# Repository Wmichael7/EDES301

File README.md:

# EDES301
Repository for EDES301 course work

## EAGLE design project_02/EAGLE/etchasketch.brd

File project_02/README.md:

# Project 02 - Etch-a-Sketch PCB

## Overview
This project contains the PCB design files for an Etch-a-Sketch device using a PocketBeagle microcontroller. The board features a USB connection, potentiometers for X/Y control, push buttons, and LEDs.

## Project Structure

### `/EAGLE`
Contains the EAGLE PCB design files:
- `etchasketch.sch` - Schematic design
- `etchasketch.brd` - Board layout
- `etchasketch.lbr` - Custom component library

### `/MFG`
Manufacturing files ready for PCB fabrication:

#### `/CAMOutputs/GerberFiles`
- Gerber files for PCB layers (top/bottom copper, soldermask, silkscreen, paste, profile)
- `gerber_job.gbrjob` - Job configuration file

#### `/CAMOutputs/DrillFiles`
- Drill files for PCB holes

#### `/CAMOutputs/Assembly`
- `etchasketch.txt` - Assembly drawing
- `PnP_etchasketch_front.txt` - Front pick-and-place file
- `PnP_etchasketch_back.txt` - Back pick-and-place file

### `/docs`
- `BOM` - Bill of Materials with component specifications

## Bill of Materials

Key components include:
- 1x PocketBeagle microcontroller
- 2x Potentiometers (for X/Y control)
- 2x Push buttons
- 3x LEDs
- 1x USB Type A receptacle connector
- Various resistors
- 4x Mounting holes
- 6x Fiducials

## Getting Started

### Design Files
Open the EAGLE schematic and board files in Autodesk EAGLE to view or modify the design:
1. Open `EAGLE/etchasketch.sch` for schematic
2. Open `EAGLE/etchasketch.brd` for board layout

### Manufacturing
The `/MFG/CAMOutputs` directory contains all files needed to manufacture the PCB:
- Send Gerber files to your PCB manufacturer
- Use the BOM to source components
- Use pick-and-place files for assembly

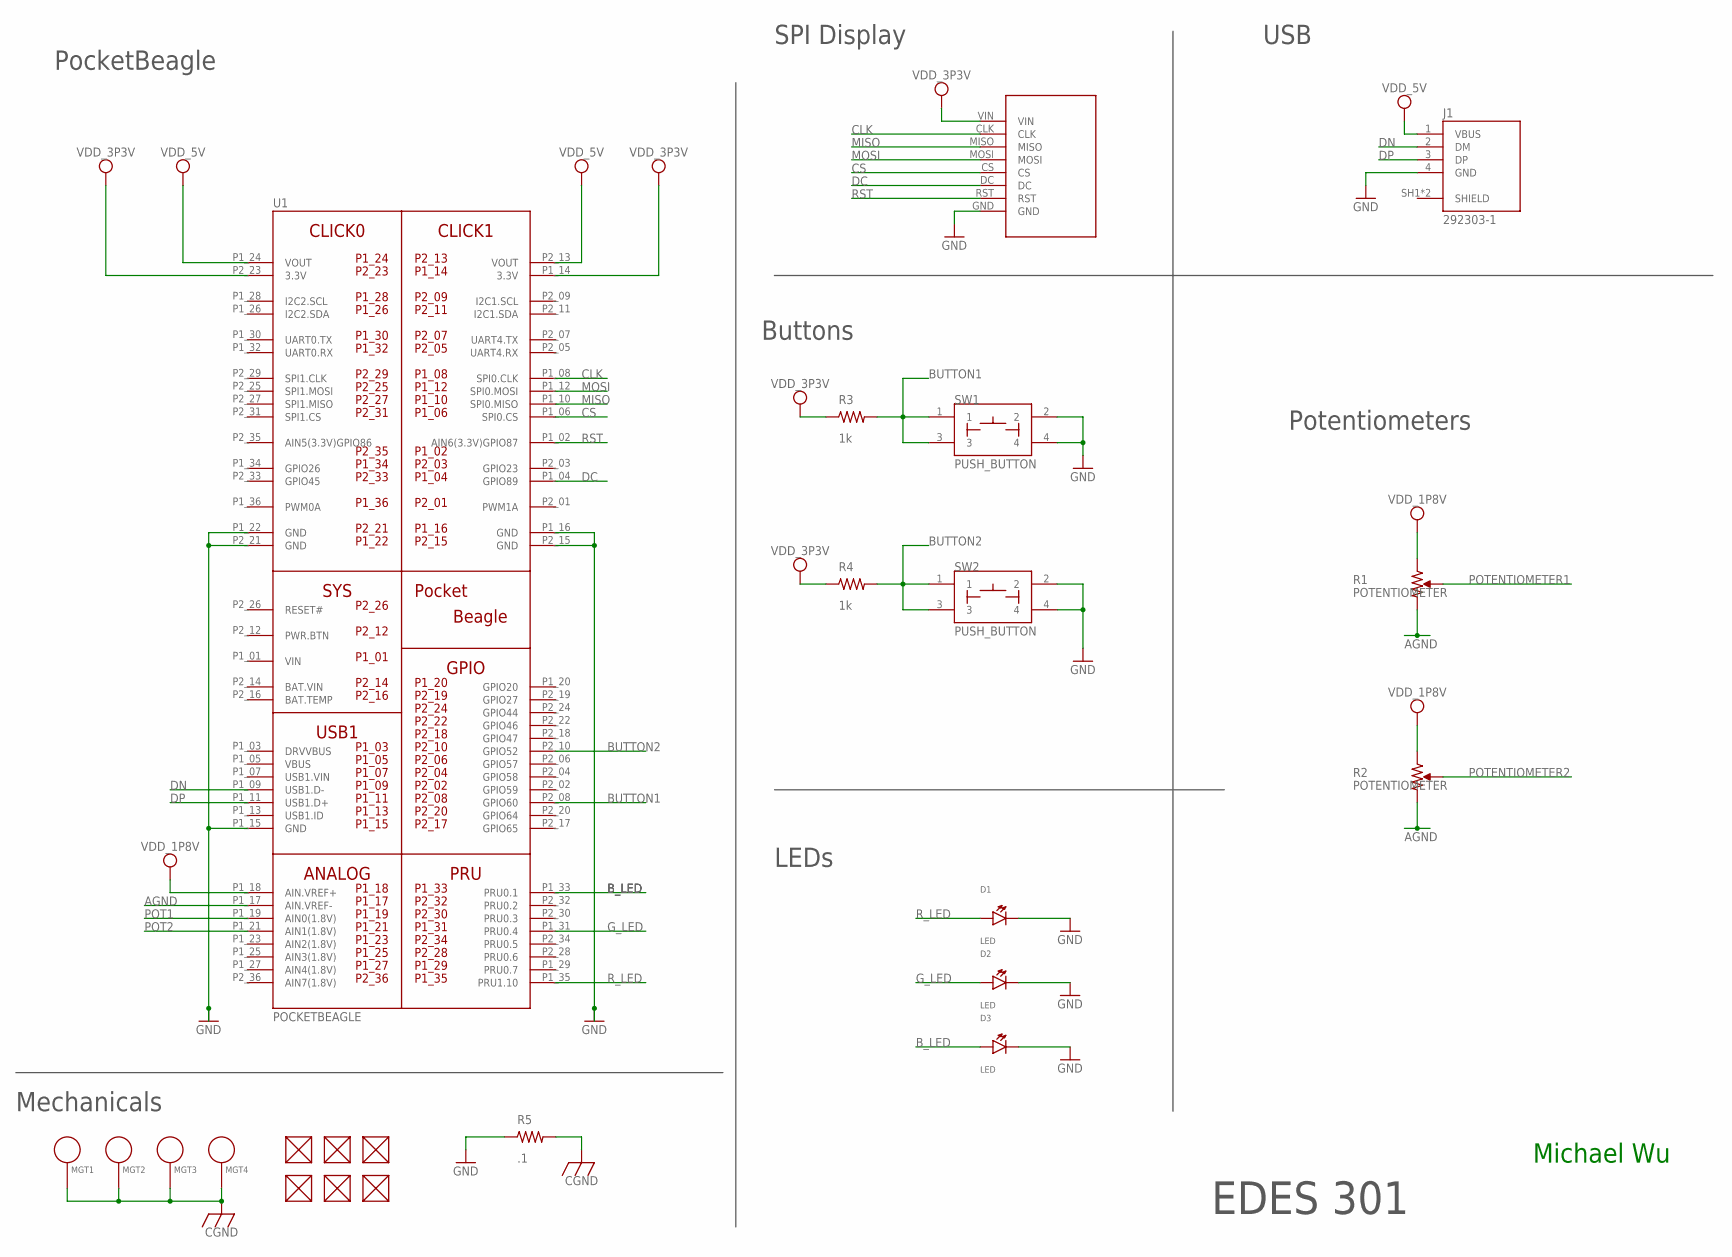
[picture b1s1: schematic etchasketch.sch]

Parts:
D1, D2, D3: LED; EIA-STD
FUD1, FUD2, FUD3, FUD4, FUD5, FUD6: FIDUCIAL; FIDUCIAL_40MIL
J1: 292303-1; TE_292303-1
MGT1, MGT2, MGT3, MGT4: MOUNTING_HOLE
R1, R2: POTENTIOMETER; POT-PO90S
R3, R4: 1k; R0603
R5: .1; R1206
SW1, SW2: PUSH_BUTTON; BUTTON_12.5MM
U1: POCKETBEAGLE
U$1: SCREEN

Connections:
AGND: R1.CW, R2.CW, U1.P1_17 (AIN.VREF-)
BAT.VIN: U1.P2_14 (BAT.VIN)
BUTTON1: R3.2, SW1.1, SW1.3, U1.P2_08 (GPIO60)
BUTTON2: R4.2, SW2.1, SW2.3, U1.P2_10 (GPIO52)
B_LED: D3.ANODE, U1.P1_33 (PRU0.1)
CGND: MGT1.P$1, MGT2.P$1, MGT3.P$1, MGT4.P$1, R5.2
CLK: U1.P1_08 (SPI0.CLK), U$1.CLK
CS: U1.P1_06 (SPI0.CS), U$1.CS
DC: U1.P1_04 (GPIO89), U$1.DC
DN: J1.2 (DM), U1.P1_09 (USB1.D-)
DP: J1.3 (DP), U1.P1_11 (USB1.D+)
GND: D1.CATHODE, D2.CATHODE, D3.CATHODE, J1.4 (GND), R5.1, SW1.2, SW1.4, SW2.2, SW2.4, U1.P1_15 (GND), U1.P1_16 (GND), U1.P1_22 (GND), U1.P2_15 (GND), U1.P2_21 (GND), U$1.GND
G_LED: D2.ANODE, U1.P1_31 (PRU0.4)
MISO: U1.P1_10 (SPI0.MISO), U$1.MISO
MOSI: U1.P1_12 (SPI0.MOSI), U$1.MOSI
POT1: U1.P1_19 (AIN0(1.8V))
POT2: U1.P1_21 (AIN1(1.8V))
POTENTIOMETER1: R1.S
POTENTIOMETER2: R2.S
RST: U1.P1_02 (AIN6(3.3V)GPIO87), U$1.RST
R_LED: D1.ANODE, U1.P1_35 (PRU1.10)
VDD_1P8V: R1.CCW, R2.CCW, U1.P1_18 (AIN.VREF+)
VDD_3P3V: R3.1, R4.1, U1.P1_14 (3.3V), U1.P2_23 (3.3V), U$1.VIN
VDD_5V: J1.1 (VBUS), U1.P1_24 (VOUT), U1.P2_13 (VOUT)
VIN: U1.P1_01 (VIN)

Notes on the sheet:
PocketBeagle
SPI Display
USB
Buttons
Potentiometers
EDES 301
Mechanicals
LEDs
Michael Wu

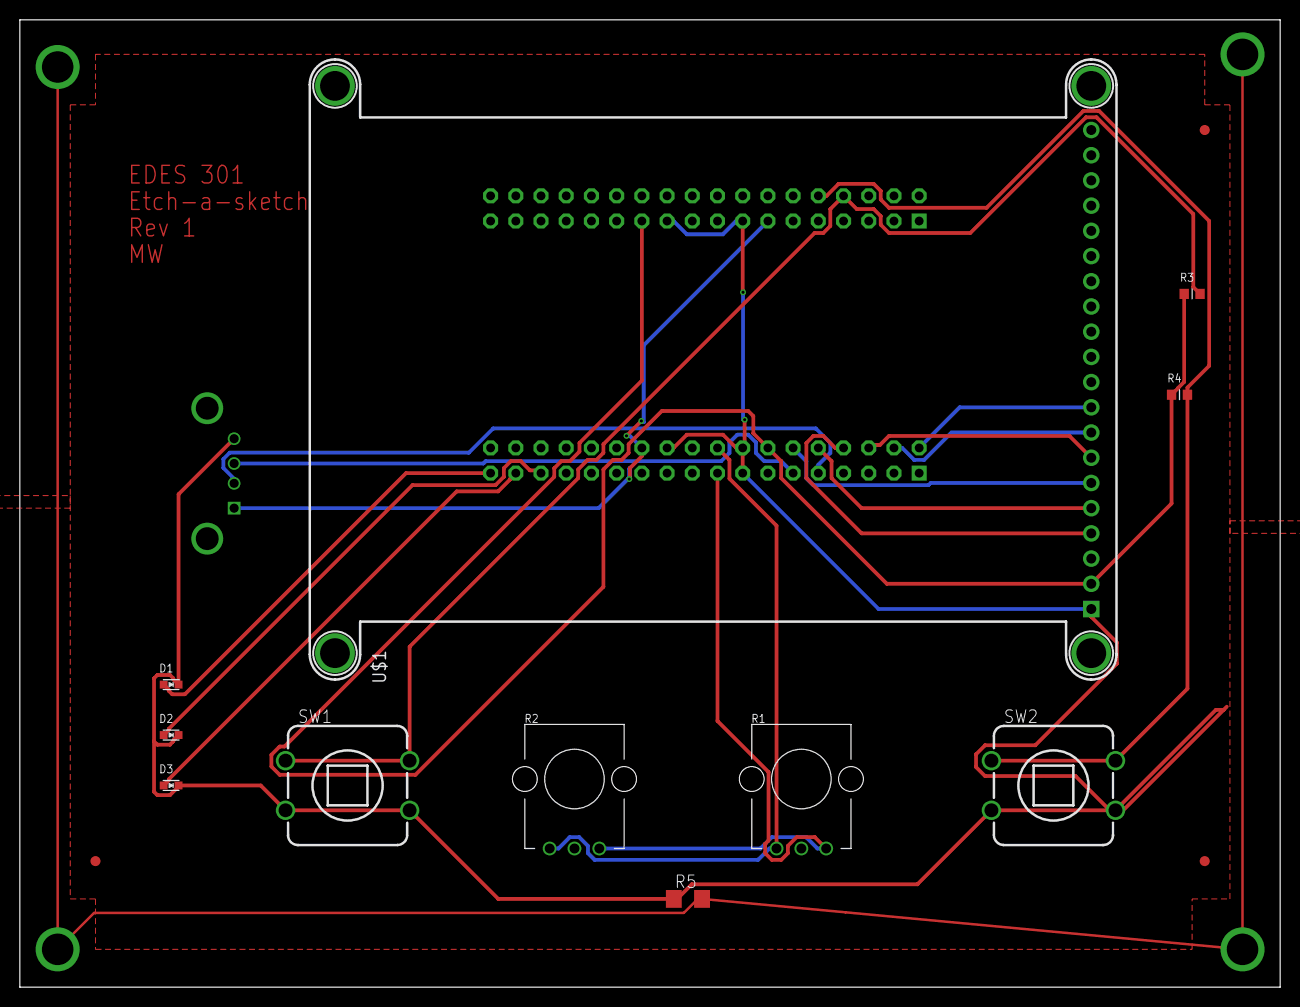
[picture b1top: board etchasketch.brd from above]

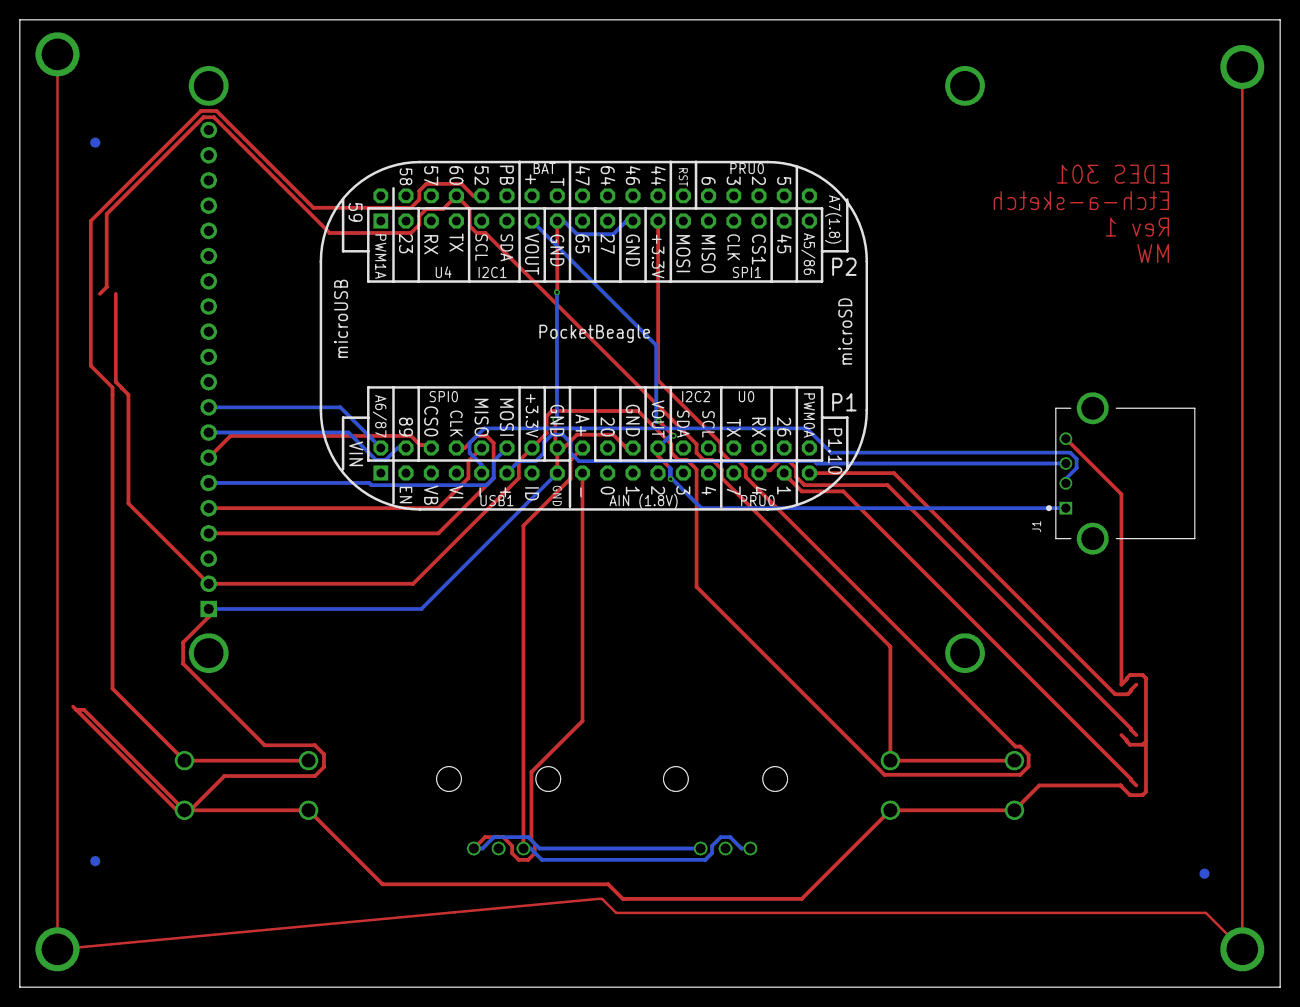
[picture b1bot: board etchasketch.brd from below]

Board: 2 copper layers, 127.0 x 97.5 mm, 23 parts (5 on the bottom side), 19 nets.

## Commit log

2025-09-24 Add course description to README
    Added a brief description for the EDES301 course repository.
2025-10-06 Add initial README with project title
2025-10-06 Update README with project proposal details
2025-10-08 you are the best
2025-12-03 project code! and README
2025-12-03 added the hackster link
2025-12-19 done with project
2025-12-19 CAM OUTPUTS
2025-12-19 readme
